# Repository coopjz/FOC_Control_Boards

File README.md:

# FOC_Control_Boards
1. generation one: g431
2. generation two: f407
- BUGS: BUCK feedback
- BUGS: Hall sensor MISO

## SoftWare
All the firmware :
url{https://github.com/coopjz/ELEC3300-Firmware }

**Author: Ed, Cooper**

**Thanks to:** Ethan, eassse, Jason

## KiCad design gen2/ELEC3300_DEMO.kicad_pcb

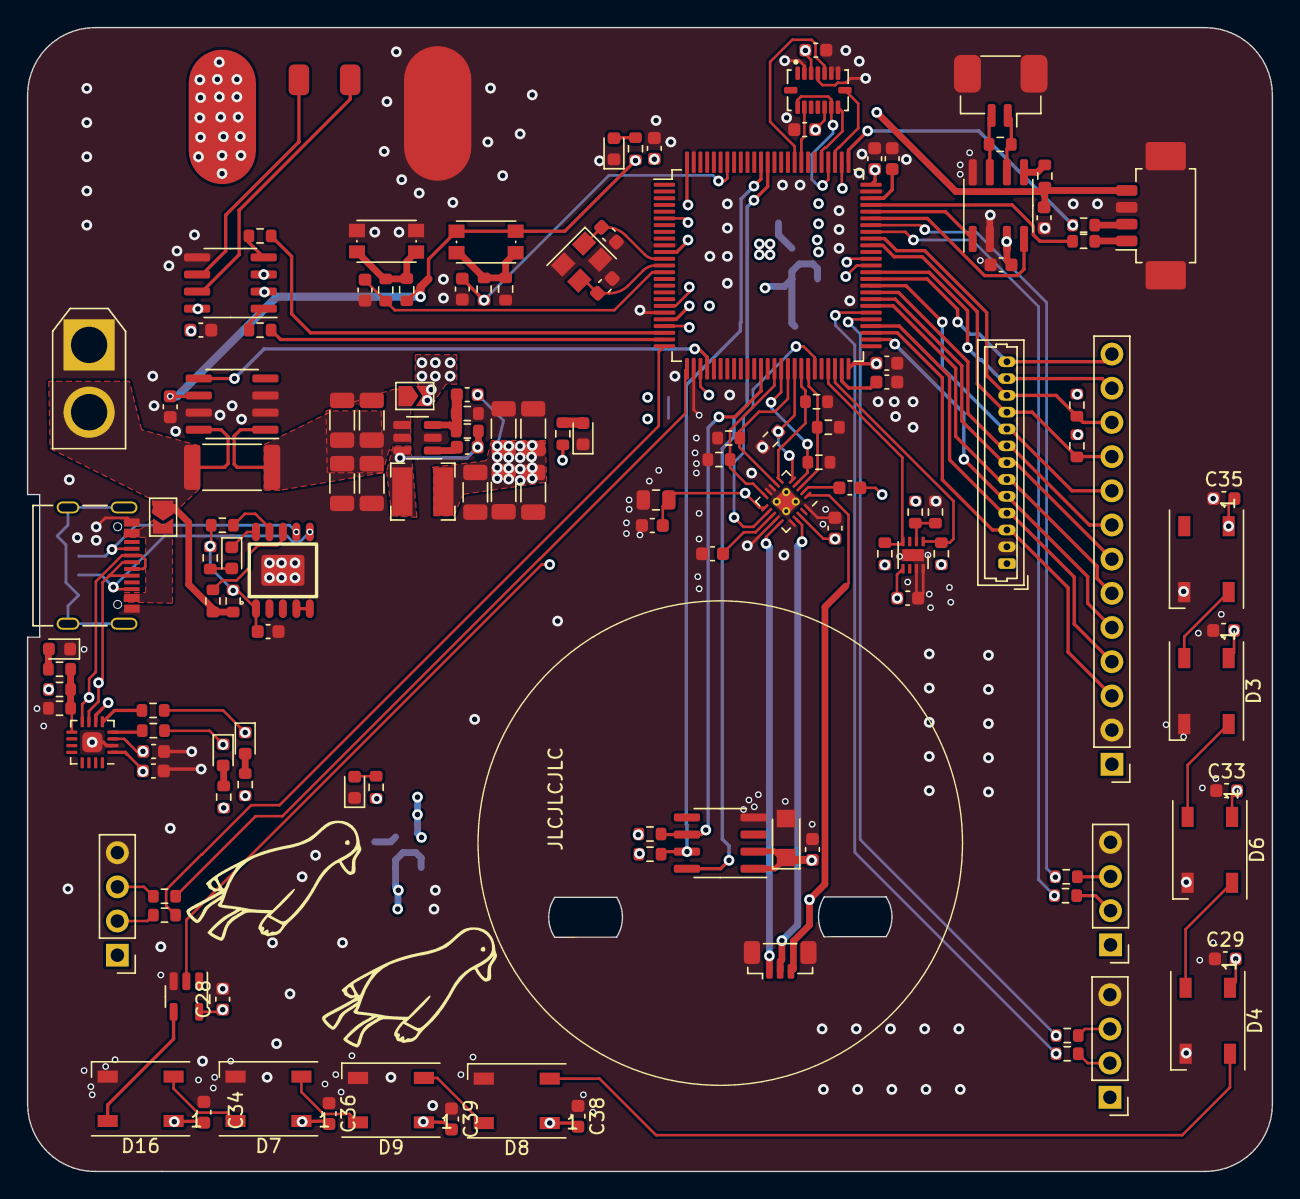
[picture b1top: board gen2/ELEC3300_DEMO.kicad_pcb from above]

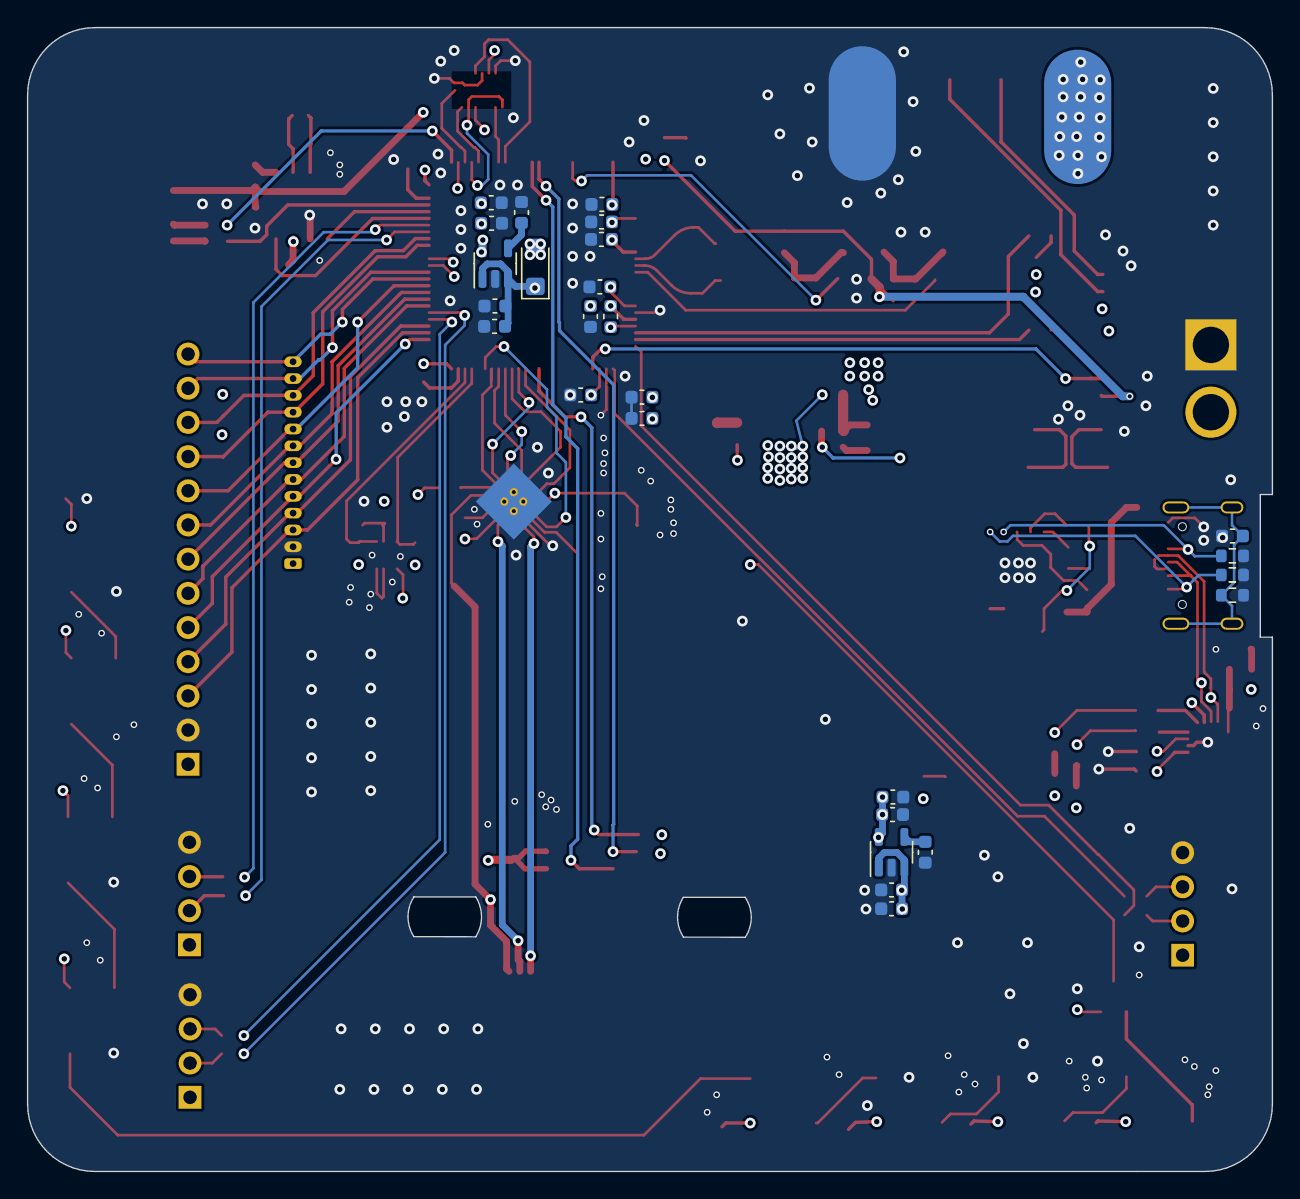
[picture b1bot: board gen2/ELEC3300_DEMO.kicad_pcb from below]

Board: 4 copper layers, 92.5 x 85.0 mm, 164 parts (26 on the bottom side), 114 nets.

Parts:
C1, C2: 20p; C_0603_1608Metric
C3, C5, C7, C9, C12, C14, C46, C47, C48, C49, C50, C51, C52, C53, C59, C60, C61, C62, C64: 100n; C_0603_1608Metric
C4, C8, C10, C15: 10u; C_0603_1608Metric
C6, C13: 10n; C_0603_1608Metric
C11, C18, C20, C22, C26: 100nF; C_0603_1608Metric
C16, C17, C56, C63: 47uF; C_1206_3216Metric
C19, C28, C29, C30, C31, C32, C33, C34, C35, C36, C37, C38, C39, C40: 0.1uF; C_0603_1608Metric
C21: 20pF; C_0603_1608Metric
C23, C24, C25, C54, C55: C_Small; C_1206_3216Metric
C27: 22uF; C_0805_2012Metric
C41: 1U; C_0603_1608Metric
C42, C43: C; C_0603_1608Metric
C44: 4.7u; C_0603_1608Metric
C45: 1u; C_0603_1608Metric
C57, C58: 2.2u; C_0603_1608Metric
D1, D2, D13, D14, D15, D17, D18: LED; LED_0603_1608Metric
D3, D4, D5, D6, D7, D8, D9, D16: WS2812B; LED_WS2812B_PLCC4_5.0x5.0mm_P3.2mm
D11: D_Schottky; D_SMF
D12: DSS34; D_SMF
J1: USB_C_Receptacle_USB2.0; USB_C_Receptacle_Palconn_UTC16-G
J2: SWD; Molex_PicoBlade_53261-0471_1x04-1MP_P1.25mm_Horizontal
J3: Conn_01x13_Pin; PinHeader_1x13_P2.54mm_Vertical
J4: Conn_01x03_MountingPin; JST_SUR_BM03B-SURS-TF_1x03-1MP_P0.80mm_Vertical
J5: Conn_01x02; GH_1x02
J6, J7, J8: Conn_01x04_Pin; PinHeader_1x04_P2.54mm_Vertical
J9: Conn_01x13; Molex_PicoBlade_53047-1310_1x13_P1.25mm_Vertical
J11: Conn_01x02_Pin; padSmall2
J12: Conn_01x02; AMASS_XT30U-M_1x02_P5.0mm_Vertical
J13: Conn_01x02_Pin; pads2
JP1, JP2: Jumper_2_Open; SolderJumper-2_P1.3mm_Open_TrianglePad1.0x1.5mm
L1: L_Small; L_Bourns-SRN4018
L3: 220r; L_0603_1608Metric
R1: 2.3k; R_0603_1608Metric
R2, R3: 5.1k; R_0603_1608Metric
R4: 53.6k; R_0603_1608Metric
R5, R24, R32, R33, R38, R39: 10k; R_0603_1608Metric
R6, R7, R8, R9, R12, R13: 330; R_0603_1608Metric
R10, R27, R35, R44, R45, R46, R47, R48, R49: 100; R_0603_1608Metric
R11, R16, R17, R34, R36, R37, R42: R; R_0603_1608Metric
R14, R15: 2.2k; R_0603_1608Metric
R18, R19, R20, R21, R22, R23: 100k; R_0603_1608Metric
R25: 120; R_0603_1608Metric
R26: Ik; R_0603_1608Metric
R28: NC; R_0603_1608Metric
R29: 0; R_0603_1608Metric
R30, R31, R40, R41: R_Small; R_0603_1608Metric
R43: 300; R_0603_1608Metric
R50: 4m; R_2512_6332Metric
SW1, SW2: SW_Push; SW_Push_1P1T_NO_CK_KMR2
U1, U5: RS3236; SOT-23-5
U2: TJA1042T-3; SOIC-8_3.9x4.9mm_P1.27mm
U3: ch343p; QFN-16-1EP_3x3mm_P0.5mm_EP1.7x1.7mm
U4: MT6701-CT; SOIC-8_3.9x4.9mm_P1.27mm
U6: SN74LV1T34DBV; SOT-23-5
U7: TMC6300; QFN-20-1EP_3x3mm_P0.4mm_EP1.65x1.65mm_ThermalVias_LargerVia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
U8: STM32F407VGTx; LQFP-100_14x14mm_P0.5mm
U9: ESSOP-10
U10: BMI088; PQFN50P450X300X100-16N
U11: SOT-23-6
U12: MAX13488EASA; SOIC-8_3.9x4.9mm_P1.27mm
U13: DFN-8-1EP_2x2mm_P0.5mm_EP0.9x1.6mm
U14: INA282; SOIC-8_3.9x4.9mm_P1.27mm
Y2: Crystal_GND24; Crystal_SMD_3225-4Pin_3.2x2.5mm

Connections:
+3.3V: C14.1, C15.1, C19.1, C22.1, C26.1, D11.1 (K), R14.2, R15.2, R16.2, R17.2, R36.1, U3.1 (VIO), U3.3 (VDD5), U3.6 (V3), U4.1 (VDD), U4.2 (MODE), U5.5 (OUT)
+5V: C4.1, C5.1, C10.1, C12.1, C18.1, C21.2, C23.2, C24.2, C25.2, C27.1, C28.1, C29.2, C30.1, C31.1, C32.1, C33.2, C34.2, C35.2, C36.2, C38.2, C39.2, C40.2, C54.2, C55.2, C61.1, C62.1, D3.1 (VDD), D4.1 (VDD), D5.1 (VDD), D6.1 (VDD), D7.1 (VDD), D8.1 (VDD), D9.1 (VDD), D12.1 (K), D16.1 (VDD), J3.1, J6.1, J7.1, J8.1, J9.1, J13.1, JP1.2 (B), L1.2, R30.1, R31.1, R34.1, R39.2, R40.1, R41.1, U1.1 (IN), U1.3 (EN), U2.3 (VCC), U5.1 (IN), U5.3 (EN), U6.5 (VCC), U7.11 (VIO/~STDBY), U7.18 (VS), U12.2 (~RE), U12.3 (~SHDN), U12.8 (VCC), U13.5 (VDD)
/LED_DATA_5V: D16.4 (DIN), U6.4 (Y)
A+: J11.2, U12.6 (A)
ADC: U8.29 (PA4), U14.5
B-: J11.1, U12.7 (B)
BOOT0: C59.1, R9.2, U8.94 (BOOT0)
CAN_H: J5.1, R25.1, U2.7 (CANH)
CAN_L: J5.2, R25.2, U2.6 (CANL)
CAN_RX: U2.4 (RXD), U8.70 (PA11)
CAN_TX: U2.1 (TXD), U8.71 (PA12)
CC1: J1.A5 (CC1), R3.1, U9.7 (CC1)
CC2: J1.B5 (CC2), R2.1, U9.6 (CC2)
CSB_ACCEL: U8.83 (PD2), U10.14 (CSB1)
CSB_GYRO: U8.84 (PD3), U10.5 (CSB2)
GND: C1.1, C2.1, C3.2, C4.2, C5.2, C6.2, C7.2, C8.2, C9.1, C10.2, C11.2, C12.2, C13.2, C14.2, C15.2, C16.1, C17.1, C18.2, C19.2, C22.2, C23.1, C24.1, C25.1, C26.2, C27.2, C28.2, C29.1, C30.2, C31.2, C33.1, C34.1, C35.1, C36.1, C37.2, C38.1, C39.1, C40.1, C41.2, C42.1, C43.1, C44.2, C45.2, C46.2, C47.2, C48.2, C49.2, C50.2, C51.2, C52.2, C53.2, C54.1, C55.1, C56.1, C57.1, C58.1, C59.2, C60.1, C61.2, C62.2, C63.1, C64.2, D3.3 (VSS), D4.3 (VSS), D5.3 (VSS), D6.3 (VSS), D7.3 (VSS), D8.3 (VSS), D9.3 (VSS), D11.2 (A), D14.1 (K), D15.1 (K), D16.3 (VSS), D17.1 (K), D18.1 (K), J1.A1 (GND), J1.A12 (GND), J1.B1 (GND), J1.B12 (GND), J2.3, J2.MP (MountPin), J3.2, J4.MP (MountPin), J5.MP (MountPin), J6.4, J7.4, J8.4, J9.2, J12.1, J13.2, R1.2, R2.2, R3.2, R5.2, R18.2, R19.2, R20.2, R21.2, R22.2, R23.2, R24.2, R38.1, R44.2, SW1.2, U1.2 (GND), U2.2 (GND), U2.8 (STB), U3.2 (GND), U3.17 (GND), U4.4 (GND), U5.2 (GND), U6.3 (GND), U7.8 (GND), U7.9 (GND), U7.14 (GND), U7.16 (BRUV), U7.20 (BRW), U7.PAD, U8.10 (VSS), U8.20 (VSSA), U8.27 (VSS), U8.74 (VSS), U8.99 (VSS), U9.0 (GND), U10.2 (NC), U10.4 (GNDA), U10.6 (GNDIO), U10.7 (PS), U11.2 (GND), U12.5 (GND), U13.7 (R), U13.8 (VSS), U13.9 (die), U14.2 (GND), U14.3 (REF2), U14.7 (REF1), Y2.2, Y2.4
I2C2_SCL: R40.2, U8.47 (PB10), U13.4 (SCL)
I2C2_SDA: R41.2, U8.48 (PB11), U13.1 (SDA)
IMU_MISO: U8.79 (PC11), U10.10 (SDO2), U10.15 (SDO1)
IMU_MOSI: U8.80 (PC12), U10.9 (SDA/SDI)
IMU_SCK: U8.78 (PC10), U10.8 (SCL/SCK)
LCD_BL: J3.9, J9.9, U8.60 (PD13)
LCD_CS: J3.6, J9.6, U8.57 (PD10)
LCD_DC: J3.7, J9.7, U8.58 (PD11)
LCD_RST: J3.8, J9.8, U8.59 (PD12)
LED_DATA_3V3: U6.2 (A), U8.77 (PA15)
MAG_CLK: R14.1, U4.7 (B/V/SCL/CLK), U8.89 (PB3)
MAG_CSN: U4.8 (Z/W/CSN), U8.88 (PD7)
MAG_DO: R15.1, U4.6 (A/U/SDA/DO), U8.37 (PB2)
MCU_3.3V: C3.1, C7.1, C8.1, C42.2, C43.2, C44.1, C45.1, C46.1, C47.1, C48.1, C49.1, C50.1, C51.1, C52.1, C53.1, C60.2, C64.1, D12.2 (A), J2.4, L3.2, R29.1, R33.1, R37.1, SW2.2, U1.5 (OUT), U8.6 (VBAT), U8.11 (VDD), U8.19 (VDD), U8.22 (VDDA), U8.28 (VDD), U8.50 (VDD), U8.75 (VDD), U8.100 (VDD), U10.3 (VDD), U10.11 (VDDIO), U14.6 (V+)
NRST: C9.2, R8.2, U8.14 (NRST)
unnamed: D1.2 (A), R16.1
unnamed: D2.2 (A), R17.1
unnamed: D3.4 (DIN), D6.2 (DOUT)
unnamed: D3.2 (DOUT), D5.4 (DIN)
unnamed: D4.4 (DIN), D8.2 (DOUT)
unnamed: D4.2 (DOUT), D6.4 (DIN)
unnamed: D7.2 (DOUT), D9.4 (DIN)
unnamed: D8.4 (DIN), D9.2 (DOUT)
unnamed: D13.2 (A), R42.2
unnamed: D13.1 (K), U9.10 (PG)
unnamed: D14.2 (A), R11.2
unnamed: D15.2 (A), R34.2
unnamed: D7.4 (DIN), D16.2 (DOUT)
unnamed: D17.2 (A), R36.2
unnamed: D18.2 (A), R37.2
unnamed: C11.1, J1.S1 (SHIELD), R1.1
unnamed: J2.1, R7.2
unnamed: J2.2, R6.2
unnamed: J4.1, U7.15 (U)
unnamed: J4.2, U7.17 (V)
unnamed: J4.3, U7.1 (W)
unnamed: J6.2, R27.2
unnamed: J6.3, R45.2
unnamed: J7.2, R48.2
unnamed: J7.3, R49.2
unnamed: J8.2, R46.2
unnamed: J8.3, R47.2
unnamed: J1.A4 (VBUS), J1.A9 (VBUS), J1.B4 (VBUS), J1.B9 (VBUS), JP2.2 (B)
unnamed: R9.1, R24.1, SW2.1
unnamed: R8.1, R33.2, SW1.1
unnamed: C6.1, U1.4 (BP)
unnamed: R29.2, U2.5 (VIO)
unnamed: R12.1, U3.5 (RXD)
unnamed: R13.1, U3.4 (TXD)
unnamed: C13.1, U5.4 (BP)
unnamed: C37.1, U7.13 (1V8OUT)
unnamed: C32.2, U7.2 (VCP)
unnamed: C58.2, U8.49 (VCAP_1)
unnamed: C57.2, U8.73 (VCAP_2)
unnamed: L3.1, U8.21 (VREF+)
unnamed: U9.4 (DP), U9.5 (DM)
unnamed: R32.1, U9.8 (VBUS)
unnamed: C20.1, U11.1 (BS)
unnamed: C21.1, R4.2, R5.1, U11.3 (FB)
unnamed: C20.2, L1.1, R4.1, U11.6 (SW)
unnamed: R10.1, U12.4 (DI)
unnamed: R35.2, U12.1 (RO)
unnamed: R38.2, R39.1, U13.2 (ADDR)
OSC_IN: C1.2, U8.12 (PH0), Y2.1
OSC_OUT: C2.2, U8.13 (PH1), Y2.3
PD_CFG1: R28.2, U9.9 (CFG1)
SPI2_MISO: J3.3, J9.3, U8.53 (PB14)
SPI2_MOSI: J3.4, J9.4, U8.54 (PB15)
SPI2_SCK: J3.5, J9.5, U8.52 (PB13)
SYS_JTCK-SWCLK: R6.1, U8.76 (PA14)
SYS_JTMS-SWDIO: R7.1, U8.72 (PA13)
TMC_DIAG: U7.12 (DIAG), U8.45 (PE14)
TMC_UH: R18.1, U7.3 (UH), U8.44 (PE13)
TMC_UL: R19.1, U7.6 (UL), U8.43 (PE12)
TMC_VH: R20.1, U7.4 (VH), U8.40 (PE9)
TMC_VL: R21.1, U7.10 (VL), U8.39 (PE8)
TMC_WH: R22.1, U7.5 (WH), U8.42 (PE11)
TMC_WL: R23.1, U7.7 (WL), U8.41 (PE10)
TP_INT: J3.12, J9.12, U8.62 (PD15)
TP_RST: J3.13, J9.13, U8.61 (PD14)
TP_SCL: J3.11, J9.11, R31.2, U8.67 (PA8)
TP_SDA: J3.10, J9.10, R30.2, U8.66 (PC9)
UART4_RX: R35.1, U8.24 (PA1)
UART4_TX: R10.2, U8.23 (PA0)
USART1_RX: R49.1, U8.69 (PA10)
USART1_TX: R48.1, U8.68 (PA9)
USART2_RX: R45.1, U8.26 (PA3)
USART2_TX: R27.1, U8.25 (PA2)
USART3_RX: R46.1, U8.56 (PD9)
USART3_TX: R47.1, U8.55 (PD8)
USART6_RX: D1.1 (K), R13.2, U8.63 (PC6)
USART6_TX: D2.1 (K), R12.2, U8.64 (PC7)
USB_D+: J1.A6 (D+), J1.B6 (D+), U3.7 (VD+)
USB_D-: J1.A7 (D-), J1.B7 (D-), U3.8 (VD-)
VBUS: C16.2, C17.2, C56.2, C63.2, JP1.1 (A), R50.2, U11.4 (EN), U11.5 (IN), U14.1 (-)
VBUS_IND: R11.1, R43.2, R44.1, U3.9 (VBUS)
VDD: C41.1, R26.1, R28.1, R42.1, U9.1 (VDD)
V_IN: J12.2, JP2.1 (A), R26.2, R32.2, R43.1, R50.1, U14.8 (+)

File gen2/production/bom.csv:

Designator,Footprint,Quantity,Value,LCSC Part #
C1,0603,1,20p,
C10,0603,1,10u,
C11,0603,1,100nF,
C12,0603,1,100n,
C13,0603,1,10n,
C14,0603,1,100n,
C15,0603,1,10u,
C16,1206,1,47uF,
C17,1206,1,47uF,
C18,0603,1,100nF,
C19,0603,1,0.1uF,
C2,0603,1,20p,
C20,0603,1,100nF,
C21,0603,1,20pF,
C22,0603,1,100nF,
C23,1206,1,C_Small,
C24,1206,1,C_Small,
C25,1206,1,C_Small,
C26,0603,1,100nF,
C27,0805,1,22uF,
C28,0603,1,0.1uF,C1591
C29,0603,1,0.1uF,C1591
C3,0603,1,100n,
C30,0603,1,0.1uF,
C31,0603,1,0.1uF,
C32,0603,1,0.1uF,
C33,0603,1,0.1uF,C1591
C34,0603,1,0.1uF,C1591
C35,0603,1,0.1uF,C1591
C36,0603,1,0.1uF,C1591
C37,0603,1,0.1uF,
C38,0603,1,0.1uF,C1591
C39,0603,1,0.1uF,C1591
C4,0603,1,10u,
C40,0603,1,0.1uF,C1591
C41,0603,1,1U,
C42,0603,1,C,
C43,0603,1,C,
C44,0603,1,4.7u,
C45,0603,1,1u,
C46,0603,1,100n,
C47,0603,1,100n,
C48,0603,1,100n,
C49,0603,1,100n,
C5,0603,1,100n,
C50,0603,1,100n,
C51,0603,1,100n,
C52,0603,1,100n,
C53,0603,1,100n,
C54,1206,1,C_Small,
C55,1206,1,C_Small,
C56,1206,1,47uF,
C57,0603,1,2.2u,
C58,0603,1,2.2u,
C59,0603,1,100n,
C6,0603,1,10n,
C60,0603,1,100n,
C61,0603,1,100n,
C62,0603,1,100n,
C63,1206,1,47uF,
C64,0603,1,100n,
C7,0603,1,100n,
C8,0603,1,10u,
C9,0603,1,100n,
D1,0603,1,LED,
D11,D_SMF,1,D_Schottky,
D12,D_SMF,1,DSS34,
D13,0603,1,LED,
D14,0603,1,LED,
D15,0603,1,LED,
"D16, D3, D4, D5, D6, D7, D8, D9",LED_WS2812B_PLCC4_5.0x5.0mm_P3.2mm,8,WS2812B,
D17,0603,1,LED,
D18,0603,1,LED,
D2,0603,1,LED,
J1,USB_C_Receptacle_Palconn_UTC16-G,1,USB_C_Receptacle_USB2.0,
J11,padSmall2,1,Conn_01x02_Pin,
J12,AMASS_XT30U-M_1x02_P5.0mm_Vertical,1,Conn_01x02,
J13,pads2,1,Conn_01x02_Pin,
J2,Molex_PicoBlade_53261-0471_1x04-1MP_P1.25mm_Horizontal,1,SWD,
J3,PinHeader_1x13_P2.54mm_Vertical,1,Conn_01x13_Pin,
J4,JST_SUR_BM03B-SURS-TF_1x03-1MP_P0.80mm_Vertical,1,Conn_01x03_MountingPin,
J5,GH_1x02,1,Conn_01x02,
"J6, J7, J8",PinHeader_1x04_P2.54mm_Vertical,3,Conn_01x04_Pin,
J9,Molex_PicoBlade_53047-1310_1x13_P1.25mm_Vertical,1,Conn_01x13,
"JP1, JP2",SolderJumper-2_P1.3mm_Open_TrianglePad1.0x1.5mm,2,Jumper_2_Open,
L1,L_Bourns-SRN4018,1,L_Small,
L3,0603,1,220r,
R1,0603,1,2.3k,
R10,0603,1,100,
R11,0603,1,R,
R12,0603,1,330,
R13,0603,1,330,
R14,0603,1,2.2k,
R15,0603,1,2.2k,
R16,0603,1,R,
R17,0603,1,R,
R18,0603,1,100k,
R19,0603,1,100k,
R2,0603,1,5.1k,
R20,0603,1,100k,
R21,0603,1,100k,
R22,0603,1,100k,
R23,0603,1,100k,
R24,0603,1,10k,
R25,0603,1,120,
R26,0603,1,Ik,
R27,0603,1,100,
R28,0603,1,NC,
R29,0603,1,0,
R3,0603,1,5.1k,
R30,0603,1,R_Small,
R31,0603,1,R_Small,
R32,0603,1,10k,
R33,0603,1,10k,
R34,0603,1,R,
R35,0603,1,100,
R36,0603,1,R,
R37,0603,1,R,
R38,0603,1,10k,
R39,0603,1,10k,
R4,0603,1,53.6k,
R40,0603,1,R_Small,
R41,0603,1,R_Small,
R42,0603,1,R,
R43,0603,1,300,
R44,0603,1,100,
R45,0603,1,100,
R46,0603,1,100,
R47,0603,1,100,
R48,0603,1,100,
R49,0603,1,100,
R5,0603,1,10k,
R50,2512,1,4m,
R6,0603,1,330,
R7,0603,1,330,
R8,0603,1,330,
R9,0603,1,330,
"SW1, SW2",SW_Push_1P1T_NO_CK_KMR2,2,SW_Push,
"U1, U5",SOT-23-5,2,RS3236,
U10,PQFN50P450X300X100-16N,1,BMI088,
U11,SOT-23-6,1,~,
U12,SOIC-8_3.9x4.9mm_P1.27mm,1,MAX13488EASA,
U13,DFN-8-1EP_2x2mm_P0.5mm_EP0.9x1.6mm,1,~,
U14,SOIC-8_3.9x4.9mm_P1.27mm,1,INA282,
U2,SOIC-8_3.9x4.9mm_P1.27mm,1,TJA1042T-3,
U3,QFN-16-1EP_3x3mm_P0.5mm_EP1.7x1.7mm,1,ch343p,
U4,SOIC-8_3.9x4.9mm_P1.27mm,1,MT6701-CT,
U6,SOT-23-5,1,SN74LV1T34DBV,C100024
U7,QFN-20-1EP_3x3mm_P0.4mm_EP1.65x1.65mm_ThermalVias_LargerViaHoles,1,TMC6300,
U8,LQFP-100_14x14mm_P0.5mm,1,STM32F407VGTx,
U9,ESSOP-10,1,~,
Y2,Crystal_SMD_3225-4Pin_3.2x2.5mm,1,Crystal_GND24,

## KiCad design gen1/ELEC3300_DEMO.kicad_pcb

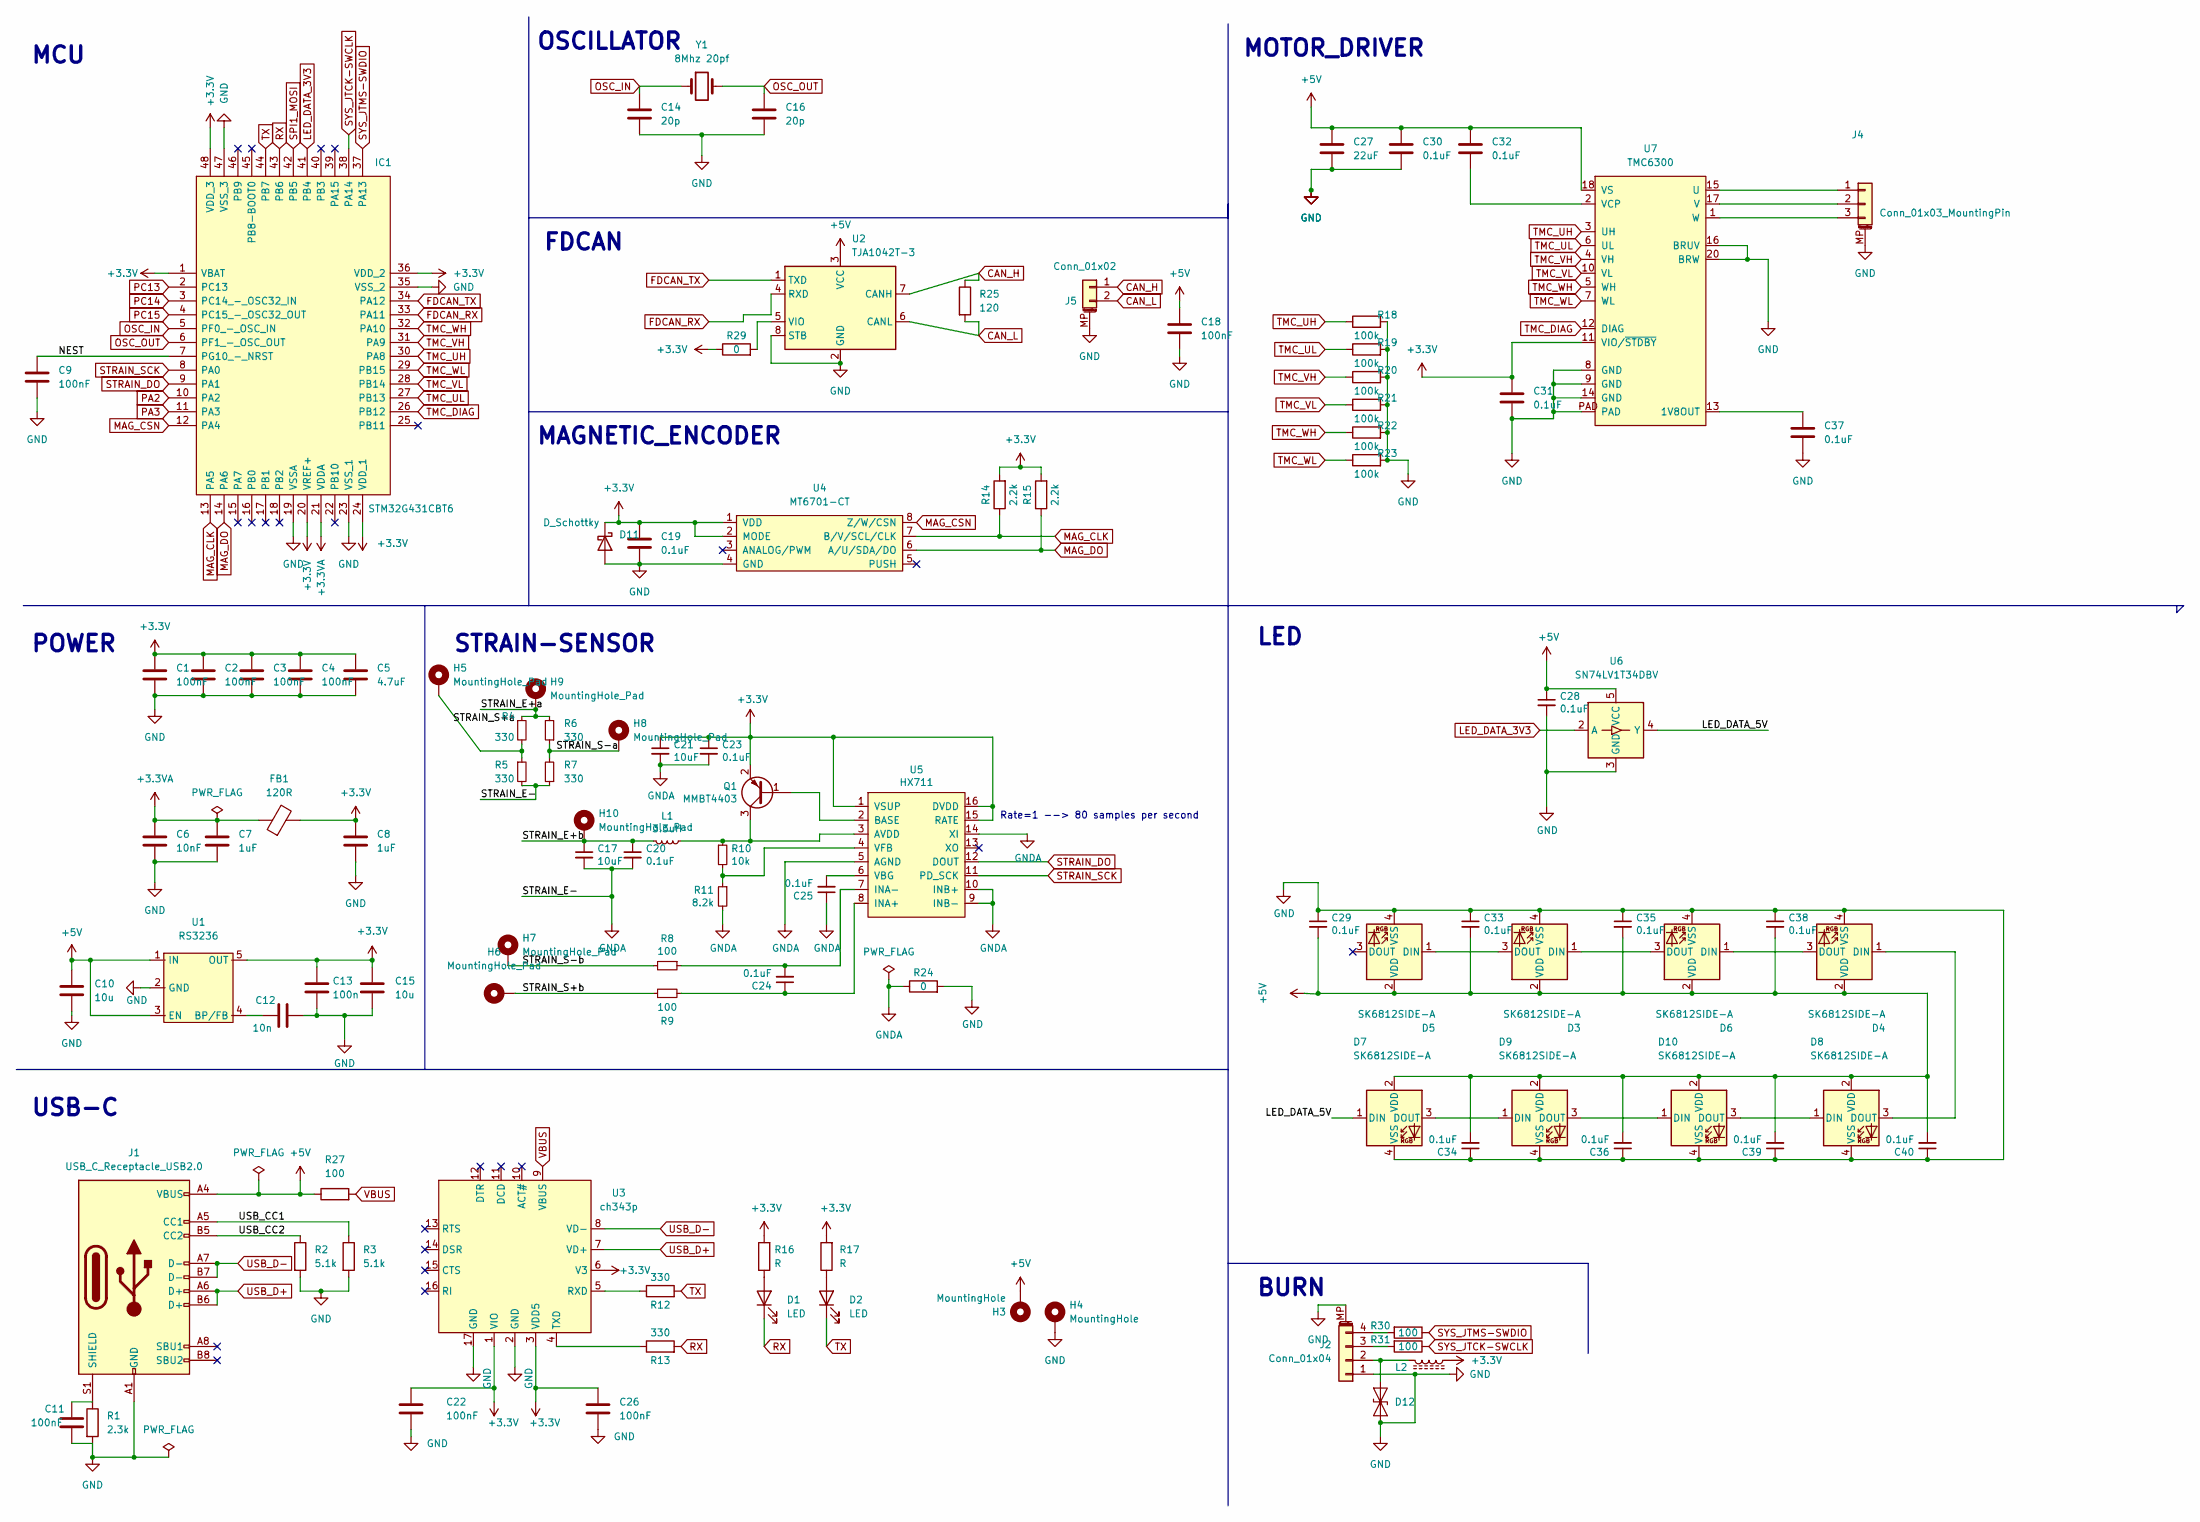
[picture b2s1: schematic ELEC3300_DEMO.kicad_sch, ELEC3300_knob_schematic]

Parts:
C1, C2, C3, C4, C9, C11, C18, C22, C26: 100nF; C_0603_1608Metric
C5: 4.7uF; C_0603_1608Metric
C6: 10nF; C_0603_1608Metric
C7, C8: 1uF; C_0603_1608Metric
C10, C15: 10u; C_0603_1608Metric
C12: 10n; C_0603_1608Metric
C13: 100n; C_0603_1608Metric
C14, C16: 20p; C_0603_1608Metric
C17, C21: 10uF; C_0603_1608Metric; LCSC C2922480
C19, C30, C31, C32, C37: 0.1uF; C_0603_1608Metric
C20, C23, C24, C25, C28, C29, C33, C34, C35, C36, C38, C39, C40: 0.1uF; C_0603_1608Metric; LCSC C1591
C27: 22uF; C_0805_2012Metric
D1, D2: LED; LED_0603_1608Metric
D3, D4, D5, D6, D7, D8, D9, D10: SK6812SIDE-A; LED_SK6812MINI_PLCC4_3.5x3.5mm_P1.75mm; Digikey 1528-4691-ND
D11: D_Schottky; D_SMF
D12: ESD9B3.3ST5G; D_SOD-123F
FB1: 120R; L_0603_1608Metric
H3, H4: MountingHole; solder_spot
H5, H6, H7, H8, H9, H10: MountingHole_Pad; pad
IC1: STM32G431CBT6; LQFP-48_7x7mm_P0.5mm; Manufacturer_Part_Number STM32G431CBT6; Mouser Part Number 511-STM32G431CBT6
J1: USB_C_Receptacle_USB2.0; USB_C_Receptacle_Palconn_UTC16-G
J2: Conn_01x04; Molex_PicoBlade_53261-0471_1x04-1MP_P1.25mm_Horizontal
J4: Conn_01x03_MountingPin; JST_SUR_BM03B-SURS-TF_1x03-1MP_P0.80mm_Vertical
J5: Conn_01x02; GH_1x02
L1: 3.3uH; L_0805_2012Metric; LCSC C307744
L2: L_Ferrite; L_0603_1608Metric
Q1: MMBT4403; SOT-23; LCSC C78864
R1: 2.3k; R_0603_1608Metric
R2, R3: 5.1k; R_0603_1608Metric
R4, R5, R6, R7: 330; R_2512_6332Metric; LCSC C19866
R8, R9: 100; R_0603_1608Metric; LCSC C319953
R10: 10k; R_0603_1608Metric; LCSC C98220
R11: 8.2k; R_0603_1608Metric; LCSC C114637
R12, R13: 330; R_0603_1608Metric
R14, R15: 2.2k; R_0603_1608Metric
R16, R17: R; R_0603_1608Metric
R18, R19, R20, R21, R22, R23: 100k; R_0603_1608Metric
R24, R29: 0; R_0603_1608Metric
R25: 120; R_0603_1608Metric
R27, R30, R31: 100; R_0603_1608Metric
U1: RS3236; SOT-23-5
U2: TJA1042T-3; SOIC-8_3.9x4.9mm_P1.27mm
U3: ch343p; QFN-16-1EP_3x3mm_P0.5mm_EP1.7x1.7mm
U4: MT6701-CT; SOIC-8_3.9x4.9mm_P1.27mm
U5: HX711; SOIC-16_3.9x9.9mm_P1.27mm; LCSC C43656
U6: SN74LV1T34DBV; SOT-23-5; LCSC C100024
U7: TMC6300; QFN-20-1EP_3x3mm_P0.4mm_EP1.65x1.65mm_ThermalVias_LargerVia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
Y1: 8Mhz 20pf; Crystal_SMD_5032-2Pin_5.0x3.2mm_HandSoldering

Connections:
+3.3VA: C6.1, C7.1, FB1.1, IC1.21 (VDDA)
+3V3: C1.1, C2.1, C3.1, C4.1, C5.1, C8.1, C13.1, C15.1, C19.1, C21.1, C22.1, C23.1, C26.1, C31.1, D11.1 (K), FB1.2, IC1.1 (VBAT), IC1.20 (VREF+), IC1.24 (VDD_1), IC1.36 (VDD_2), IC1.48 (VDD_3), L2.1, Q1.2 (E), R14.2, R15.2, R16.2, R17.2, R29.1, U1.5 (OUT), U3.1 (VIO), U3.3 (VDD5), U3.6 (V3), U4.1 (VDD), U4.2 (MODE), U5.1 (VSUP), U5.15 (RATE), U5.16 (DVDD), U7.11 (VIO/~STDBY)
+5V: C10.1, C18.1, C27.1, C28.1, C29.2, C30.1, C32.1, C33.2, C34.2, C35.2, C36.2, C38.2, C39.2, C40.2, D3.2 (VDD), D4.2 (VDD), D5.2 (VDD), D6.2 (VDD), D7.2 (VDD), D8.2 (VDD), D9.2 (VDD), D10.2 (VDD), H3.1, J1.A4 (VBUS), J1.A9 (VBUS), J1.B4 (VBUS), J1.B9 (VBUS), R27.1, U1.1 (IN), U1.3 (EN), U2.3 (VCC), U6.5 (VCC), U7.18 (VS)
/LED_DATA_5V: D7.1 (DIN), U6.4 (Y)
/NEST: C9.1, IC1.7 (PG10_-_NRST)
/STRAIN_E+a: H9.1, R4.1, R6.2
/STRAIN_E+b: C17.1, C20.1, H10.1, L1.2
/STRAIN_S+b: H6.1, R9.1
/STRAIN_S-a: H8.1, R6.1, R7.2
/STRAIN_S-b: H7.1, R8.2
/USB_CC1: J1.A5 (CC1), R3.1
/USB_CC2: J1.B5 (CC2), R2.1
CAN_H: J5.1, R25.1, U2.7 (CANH)
CAN_L: J5.2, R25.2, U2.6 (CANL)
FDCAN_RX: IC1.33 (PA11), U2.4 (RXD)
FDCAN_TX: IC1.34 (PA12), U2.1 (TXD)
GND: C1.2, C2.2, C3.2, C4.2, C5.2, C6.2, C7.2, C8.2, C9.2, C10.2, C11.2, C12.2, C13.2, C14.2, C15.2, C16.2, C18.2, C19.2, C22.2, C26.2, C27.2, C28.2, C29.1, C30.2, C31.2, C33.1, C34.1, C35.1, C36.1, C37.2, C38.1, C39.1, C40.1, D3.4 (VSS), D4.4 (VSS), D5.4 (VSS), D6.4 (VSS), D7.4 (VSS), D8.4 (VSS), D9.4 (VSS), D10.4 (VSS), D11.2 (A), D12.1 (A1), H4.1, IC1.19 (VSSA), IC1.23 (VSS_1), IC1.35 (VSS_2), IC1.47 (VSS_3), J1.A1 (GND), J1.A12 (GND), J1.B1 (GND), J1.B12 (GND), J2.1, J2.MP (MountPin), J4.MP (MountPin), J5.MP (MountPin), R1.2, R2.2, R3.2, R18.2, R19.2, R20.2, R21.2, R22.2, R23.2, R24.2, U1.2 (GND), U2.2 (GND), U2.8 (STB), U3.2 (GND), U3.17 (GND), U4.4 (GND), U6.3 (GND), U7.8 (GND), U7.9 (GND), U7.14 (GND), U7.16 (BRUV), U7.20 (BRW), U7.PAD
GNDA: C17.2, C20.2, C21.2, C23.2, C25.1, R5.2, R7.1, R11.2, R24.1, U5.5 (AGND), U5.9 (INB-), U5.10 (INB+), U5.14 (XI)
LED_DATA_3V3: IC1.41 (PB4), U6.2 (A)
MAG_CLK: IC1.13 (PA5), R14.1, U4.7 (B/V/SCL/CLK)
MAG_CSN: IC1.12 (PA4), U4.8 (Z/W/CSN)
MAG_DO: IC1.14 (PA6), R15.1, U4.6 (A/U/SDA/DO)
unnamed: C11.1, J1.S1 (SHIELD), R1.1
unnamed: C12.1, U1.4 (BP/FB)
unnamed: C24.1, R9.2, U5.8 (INA+)
unnamed: C24.2, R8.1, U5.7 (INA-)
unnamed: C25.2, U5.6 (VBG)
unnamed: C32.2, U7.2 (VCP)
unnamed: C37.1, U7.13 (1V8OUT)
unnamed: D1.2 (A), R16.1
unnamed: D2.2 (A), R17.1
unnamed: D3.1 (DIN), D6.3 (DOUT)
unnamed: D3.3 (DOUT), D5.1 (DIN)
unnamed: D4.1 (DIN), D8.3 (DOUT)
unnamed: D4.3 (DOUT), D6.1 (DIN)
unnamed: D7.3 (DOUT), D9.1 (DIN)
unnamed: D9.3 (DOUT), D10.1 (DIN)
unnamed: D8.1 (DIN), D10.3 (DOUT)
unnamed: D12.2 (A2), J2.2, L2.2
unnamed: J2.3, R31.2
unnamed: J2.4, R30.2
unnamed: J4.1, U7.15 (U)
unnamed: J4.2, U7.17 (V)
unnamed: J4.3, U7.1 (W)
unnamed: L1.1, Q1.3 (C), R10.1, U5.3 (AVDD)
unnamed: Q1.1 (B), U5.2 (BASE)
unnamed: H5.1, R4.2, R5.1
unnamed: R10.2, R11.1, U5.4 (VFB)
unnamed: R12.1, U3.5 (RXD)
unnamed: R13.1, U3.4 (TXD)
unnamed: R29.2, U2.5 (VIO)
OSC_IN: C14.1, IC1.5 (PF0_-_OSC_IN), Y1.1
OSC_OUT: C16.1, IC1.6 (PF1_-_OSC_OUT), Y1.2
PA2: IC1.10 (PA2)
PA3: IC1.11 (PA3)
PC13: IC1.2 (PC13)
PC14: IC1.3 (PC14_-_OSC32_IN)
PC15: IC1.4 (PC15_-_OSC32_OUT)
RX: D1.1 (K), IC1.43 (PB6), R13.2
SPI1_MOSI: IC1.42 (PB5)
STRAIN_DO: IC1.9 (PA1), U5.12 (DOUT)
STRAIN_SCK: IC1.8 (PA0), U5.11 (PD_SCK)
SYS_JTCK-SWCLK: IC1.38 (PA14), R31.1
SYS_JTMS-SWDIO: IC1.37 (PA13), R30.1
TMC_DIAG: IC1.26 (PB12), U7.12 (DIAG)
TMC_UH: IC1.30 (PA8), R18.1, U7.3 (UH)
TMC_UL: IC1.27 (PB13), R19.1, U7.6 (UL)
TMC_VH: IC1.31 (PA9), R20.1, U7.4 (VH)
TMC_VL: IC1.28 (PB14), R21.1, U7.10 (VL)
TMC_WH: IC1.32 (PA10), R22.1, U7.5 (WH)
TMC_WL: IC1.29 (PB15), R23.1, U7.7 (WL)
TX: D2.1 (K), IC1.44 (PB7), R12.2
USB_D+: J1.A6 (D+), J1.B6 (D+), U3.7 (VD+)
USB_D-: J1.A7 (D-), J1.B7 (D-), U3.8 (VD-)
VBUS: R27.2, U3.9 (VBUS)

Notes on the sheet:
USB-C
MAGNETIC_ENCODER
STRAIN-SENSOR
MOTOR_DRIVER
Rate=1 --> 80 samples per second
LED
BURN
FDCAN
OSCILLATOR
MCU
POWER

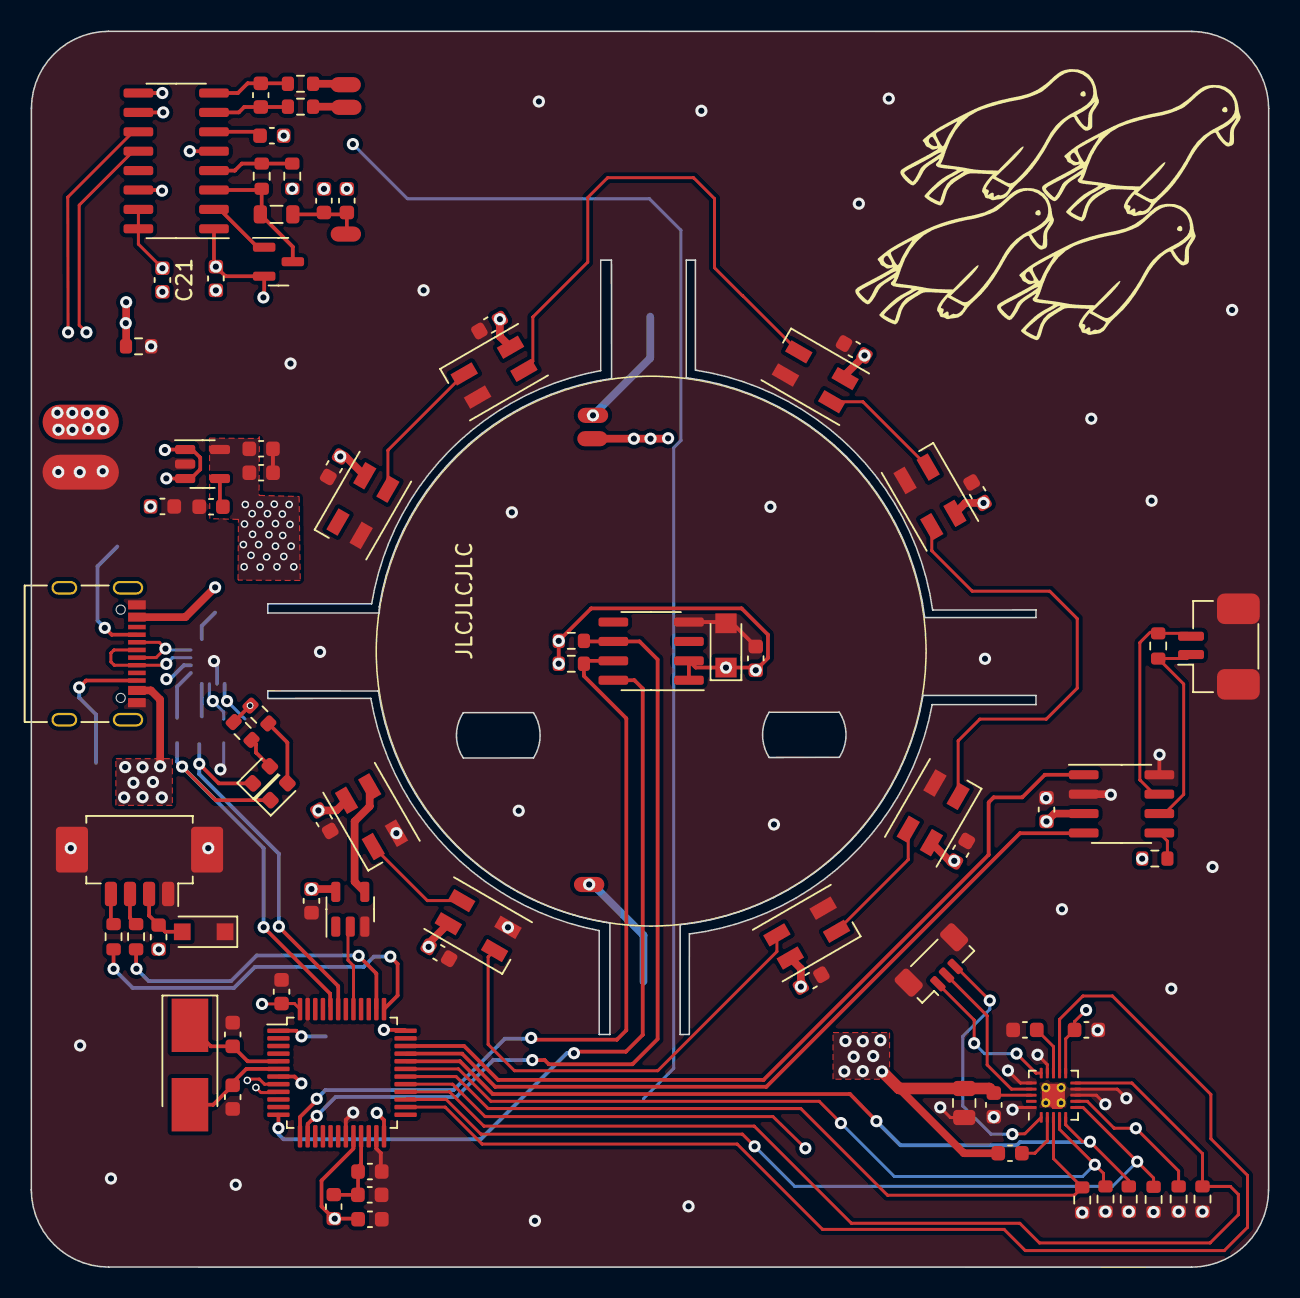
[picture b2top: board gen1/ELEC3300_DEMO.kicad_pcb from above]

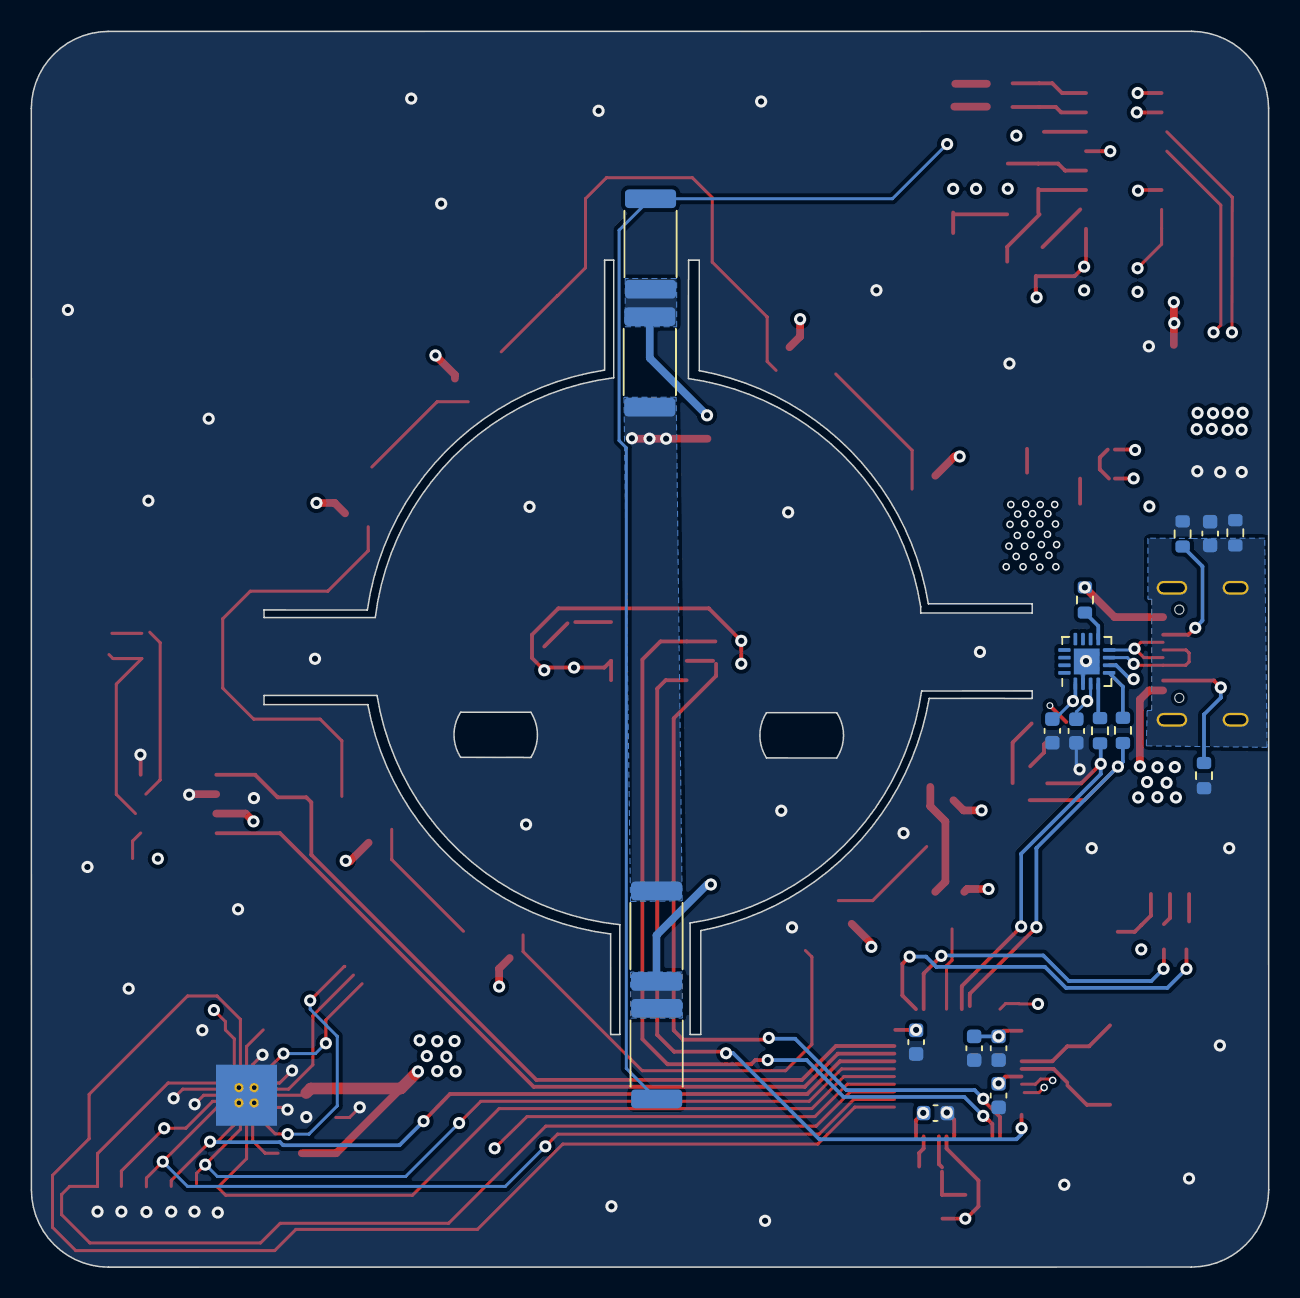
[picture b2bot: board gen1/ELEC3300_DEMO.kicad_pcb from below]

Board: 4 copper layers, 81.0 x 80.9 mm, 106 parts (19 on the bottom side), 69 nets.

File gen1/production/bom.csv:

Designator,Footprint,Quantity,Value,LCSC Part #
C1,0603,1,100nF,
C10,0603,1,10u,
C11,0603,1,100nF,
C12,0603,1,10n,
C13,0603,1,100n,
C14,0603,1,20p,
C15,0603,1,10u,
C16,0603,1,20p,
C17,0603,1,10uF,C2922480
C18,0603,1,100nF,
C19,0603,1,0.1uF,
C2,0603,1,100nF,
C20,0603,1,0.1uF,C1591
C21,0603,1,10uF,C2922480
C22,0603,1,100nF,
C23,0603,1,0.1uF,C1591
C24,0603,1,0.1uF,C1591
C25,0603,1,0.1uF,C1591
C26,0603,1,100nF,
C27,0805,1,22uF,
C28,0603,1,0.1uF,C1591
C29,0603,1,0.1uF,C1591
C3,0603,1,100nF,
C30,0603,1,0.1uF,
C31,0603,1,0.1uF,
C32,0603,1,0.1uF,
C33,0603,1,0.1uF,C1591
C34,0603,1,0.1uF,C1591
C35,0603,1,0.1uF,C1591
C36,0603,1,0.1uF,C1591
C37,0603,1,0.1uF,
C38,0603,1,0.1uF,C1591
C39,0603,1,0.1uF,C1591
C4,0603,1,100nF,
C40,0603,1,0.1uF,C1591
C5,0603,1,4.7uF,
C6,0603,1,10nF,
C7,0603,1,1uF,
C8,0603,1,1uF,
C9,0603,1,100nF,
D1,0603,1,LED,
"D10, D3, D4, D5, D6, D7, D8, D9",LED_SK6812MINI_PLCC4_3.5x3.5mm_P1.75mm,8,SK6812SIDE-A,C2890037
D11,D_SMF,1,D_Schottky,
D12,D_SOD-123F,1,ESD9B3.3ST5G,
D2,0603,1,LED,
FB1,0603,1,120R,
"H10, H5, H6, H7, H8, H9",pad,6,MountingHole_Pad,
"H3, H4",solder_spot,2,MountingHole,
IC1,LQFP-48_7x7mm_P0.5mm,1,STM32G431CBT6,
J1,USB_C_Receptacle_Palconn_UTC16-G,1,USB_C_Receptacle_USB2.0,
J2,Molex_PicoBlade_53261-0471_1x04-1MP_P1.25mm_Horizontal,1,Conn_01x04,
J4,JST_SUR_BM03B-SURS-TF_1x03-1MP_P0.80mm_Vertical,1,Conn_01x03_MountingPin,
J5,GH_1x02,1,Conn_01x02,
L1,0805,1,3.3uH,C307744
L2,0603,1,L_Ferrite,
Q1,SOT-23,1,MMBT4403,C78864
R1,0603,1,2.3k,
R10,0603,1,10k,C98220
R11,0603,1,8.2k,C114637
R12,0603,1,330,
R13,0603,1,330,
R14,0603,1,2.2k,
R15,0603,1,2.2k,
R16,0603,1,R,
R17,0603,1,R,
R18,0603,1,100k,
R19,0603,1,100k,
R2,0603,1,5.1k,
R20,0603,1,100k,
R21,0603,1,100k,
R22,0603,1,100k,
R23,0603,1,100k,
R24,0603,1,0,
R25,0603,1,120,
R27,0603,1,100,
R29,0603,1,0,
R3,0603,1,5.1k,
R30,0603,1,100,
R31,0603,1,100,
R4,2512,1,330,C19866
R5,2512,1,330,C19866
R6,2512,1,330,C19866
R7,2512,1,330,C19866
R8,0603,1,100,C319953
R9,0603,1,100,C319953
U1,SOT-23-5,1,RS3236,
U2,SOIC-8_3.9x4.9mm_P1.27mm,1,TJA1042T-3,
U3,QFN-16-1EP_3x3mm_P0.5mm_EP1.7x1.7mm,1,ch343p,
U4,SOIC-8_3.9x4.9mm_P1.27mm,1,MT6701-CT,
U5,SOIC-16_3.9x9.9mm_P1.27mm,1,HX711,C43656
U6,SOT-23-5,1,SN74LV1T34DBV,C100024
U7,QFN-20-1EP_3x3mm_P0.4mm_EP1.65x1.65mm_ThermalVias_LargerViaHoles,1,TMC6300,
Y1,Crystal_SMD_5032-2Pin_5.0x3.2mm_HandSoldering,1,8Mhz 20pf ,

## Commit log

2023-05-09 add kicad proj of 2 gens
